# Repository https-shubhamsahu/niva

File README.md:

<p align="center">
  <a href="https://https-shubhamsahu.github.io/niva/"><b>Live dashboard</b></a> ·
  <a href="./startup/niva%20arduino/README.md">Firmware</a> ·
  <a href="./hardware/outputs/NIVA-3D-engineering-prototype/README.md">Rev C.1 hardware</a> ·
  <a href="./startup/niva%20web/src/utils/biomechanicsEngine.ts">Scoring rules</a>
</p>

> Three projects share this insole: the Niva startup, the Aavishkar 2026–27 research entry, and the SIH 2026 problem statement 26213. See [PROJECTS.md](PROJECTS.md) for what belongs to which.

Niva is a smart insole for gait screening. An ESP32 reads four force pads, a piezo disc under the heel and an MPU6050, then streams 20 frames a second to a React dashboard and a Flutter app. Each gait phase, score and alert comes from a threshold in one TypeScript file, so you can point at the exact reading that set off an alert. Niva was shown at Automation Expo in July 2026.

> **Status:** the bench build runs today. The Rev C.1 wearable pod is designed, routed and DRC-clean in KiCad, but it hasn't been built or measured yet. Niva is a research and screening prototype. It isn't a medical device.

## Bench build

The active sketch is [`startup/niva arduino/niva_hardware/niva_hardware.ino`](./startup/niva%20arduino/niva_hardware/niva_hardware.ino).

| Signal | ESP32 pin | Notes |
|---|---|---|
| FSR heel | GPIO 32 | ADC1_CH4 |
| FSR inner (1st metatarsal) | GPIO 33 | ADC1_CH5 |
| FSR outer (5th metatarsal) | GPIO 34 | ADC1_CH6 |
| FSR toe | GPIO 35 | ADC1_CH7 |
| Piezo heel disc | GPIO 36 | ADC1_CH0, the impact channel |
| I2C SDA | GPIO 21 | MPU6050 at `0x68`, SH1106 OLED at `0x3C` |
| I2C SCL | GPIO 22 | shared bus |
| Status LED | GPIO 2 | blinks during tare |

What the firmware does each frame:

- reads every ADC channel 16 times at 12 bits and averages the result
- subtracts a zero-load tare (60 samples, saved in NVS, redone when you send `calibrate` or `tare` over WebSocket or Serial)
- reads pitch, roll and accZ from the MPU6050
- sends one frame every 50 ms to your WebSocket clients and the USB port
- shows Wi-Fi state, tare progress and live channel bars on the OLED

You set up Wi-Fi through a WiFiManager captive portal (`NIVA-GaitGuard-AP`), and the board answers at `ws://niva.local:81` over mDNS.

JSON over WebSocket (`ws://<esp32-ip>:81`):

```json
{"heel":42.00,"inner":68.00,"outer":31.00,"toe":27.00,"piezo":176.00,"pitch":-2.40,"roll":1.30,"accZ":9.72}
```

CSV over USB Serial at 115200 baud:

```text
H,I,O,T,Piezo,Pitch,Roll,AccZ
```

The simpler sketch, `esp32_gaitguard_wifi_manager`, uses hardcoded Wi-Fi credentials and doesn't drive the IMU or the OLED. BLE isn't in any sketch, and the IMU in firmware is the MPU6050 (you won't find BMI270 code here).

## How a step gets scored

The web app runs these rules on every frame in [`biomechanicsEngine.ts`](./startup/niva%20web/src/utils/biomechanicsEngine.ts), and there's no trained model in it. The Flutter app times strides from the firmware's contact edges instead, in [`gait_timing_engine.dart`](./startup/niva%20flutter/lib/core/engine/gait_timing_engine.dart). Here are the web rules, with the default values from the code, so you can check any number on the dashboard by hand:

| Output | Rule |
|---|---|
| Tare check | The first 30 frames must be steady: load range 8 or less, mean load 55 or less, tilt 7 or less, impact 60 or less. After 60 frames it carries on without a baseline. |
| Smoothing | EMA with α = 0.1, a deadband of 2.5 on pressure and 0.8 on angles |
| Contact | stance while the filtered total is above 45 |
| Step | piezo above 200, heel above 80, heel rising by more than 8, and the foot was in swing |
| Cadence | 60 divided by the time between heel strikes (0.2 s to 3 s) |
| Phase | `HEEL_STRIKE` heel > 80 and toe < 40; `MID_STANCE` heel, inner and outer > 50; `TOE_OFF` toe > 80 and heel < 30; `SWING` total < 20 |
| Centre of pressure | load-weighted average of the four pad positions |
| Stability score | 100 - 9 × tilt - 30 × impact level, clamped to 0 to 100 |
| Flags | supination risk when roll > 8 and outer > inner; heel-dominant gait when the heel carries over 70 % of the load for 5 frames; high sway when tilt reaches 6; ischemic pressure risk when the static-load integral passes 50 |

## Rev C.1 wearable pod

The next build swaps the dev board for a pod you wear on the lower shin: ESP32-C3, an MCP3208 ADC, an LSM6DSO32 IMU, a removable battery cartridge, one button and one light. A desk dock charges the cartridges. Every part comes out of a script (FreeCAD 1.1, KiCad 9, Blender 4.5), so you can rebuild the whole design from `hardware/work/`.

<table>
  <tr>
    <td width="50%" valign="top"></td>
    <td width="50%" valign="top"></td>
  </tr>
  <tr>
    <td width="50%" valign="top"></td>
    <td width="50%" valign="top"></td>
  </tr>
</table>

These are CAD renders, not photos. The signal chain inside the pod:

| Board | Size and layers | Routing | KiCad ERC / DRC |
|---|---|---|---|
| Pod | 34 × 48 × 1.0 mm, 4 layers, In1 = GND plane | GND fan-out, Freerouting signals, pours; 547 segments, 126 vias | ERC 0 errors; DRC 0 errors, 0 unconnected |
| Cartridge strip | 3.4 × 30 × 0.8 mm, 2 layers | hand-routed | 0 / 0 |
| Dock | 58 × 56 × 1.6 mm, 2 layers | Freerouting and GND pours | 0 / 0 |
| Insole flex R and L | 0.12 mm polyimide, F.Cu only underfoot | generated paired lanes | 0 / 0 |

What's still open: nothing has been printed, built, powered or measured. RF, sealing, skin contact, cleaning and FSR characterisation are untested, and nobody outside the project has reviewed the design. A clean ERC and DRC is an automated check. It isn't a design review. The pod has a bare-PCB first-article Gerber set for bench bring-up; the rest are review-only. The full list is in [`VERIFICATION-PLAN.md`](./hardware/outputs/NIVA-3D-engineering-prototype/VERIFICATION-PLAN.md) and the [hardware README](./hardware/outputs/NIVA-3D-engineering-prototype/README.md).

## Run it

Don't have the hardware? Open the [live dashboard](https://https-shubhamsahu.github.io/niva/) and switch to **Simulation**. It streams generated gait for six modes (Normal, Parkinson, Stroke, Neuropathy, Foot Drop, Ataxia) through the same engine. The simulated patterns are synthetic, so don't read them as patient data.

Install only what you need for the part you're running:

- **Web:** Node.js 22+ and npm
- **Flutter:** Flutter SDK (Dart 3.3+)
- **Firmware:** Arduino IDE (or another ESP32 Arduino toolchain) with ESP32 board support

### Web dashboard (`niva web`)

```bash
cd "startup/niva web"
npm install
# if peer dependency conflicts appear:
npm install --legacy-peer-deps
npm run dev
```

Other scripts:

```bash
npm run build
npm run preview
npm run lint
```

Optional environment file, `startup/niva web/.env.local`:

```bash
VITE_ESP32_WS_URL=ws://<esp32-ip>:81
VITE_ESP32_WS_RELAY_URL=wss://<your-relay-domain>/ws
VITE_ESP32_WS_RELAY_TARGET_KEY=target
VITE_DATASET_UPLOAD_URL=https://your-api.example.com/upload
VITE_DATASET_UPLOAD_TOKEN=your_optional_bearer_token
```

Optional WebSocket relay, needed when an HTTPS dashboard has to reach a `ws://` ESP32:

```bash
cd "startup/niva web/relay"
npm install
npm start
```

### Flutter app (`niva flutter`)

```bash
cd "startup/niva flutter"
flutter pub get
flutter analyze
flutter test
flutter run
```

The ESP32 endpoint, relay URL and upload URL are runtime settings on the Device tab, not build-time env files.

### Firmware (`niva arduino`)

Open a sketch in Arduino IDE, install the libraries listed in [`startup/niva arduino/README.md`](./startup/niva%20arduino/README.md) (WiFiManager, WebSockets, U8g2), select an ESP32 board and upload:

- **Active hardware sketch:** `startup/niva arduino/niva_hardware/niva_hardware.ino`
- **Simpler hardcoded Wi-Fi sketch:** `startup/niva arduino/esp32_gaitguard_wifi_manager/esp32_gaitguard_wifi_manager.ino`

Open Serial Monitor at **115200** baud, note the printed IP, and point the Flutter Device tab or the web Settings page at `ws://<ESP32_IP>:81`.

## Stack

- **Web:** React 19, TypeScript, Vite, Tailwind, Recharts, IndexedDB, Web Serial
- **Flutter:** Riverpod, Hive, `web_socket_channel`, `fl_chart`
- **Relay:** Node.js and `ws`
- **Deploy:** GitHub Pages through [`.github/workflows/deploy-pages.yml`](./.github/workflows/deploy-pages.yml), which builds `niva web`

There's no application server or database. Your datasets stay in your browser (IndexedDB) or on your phone (Hive). CSV upload to an external research API is optional.

## Repository layout

| Directory | Contents |
|---|---|
| `startup/niva arduino/` | ESP32 firmware: ADC acquisition, tare, IMU, OLED, Wi-Fi and WebSocket |
| `startup/niva web/` | Clinician dashboard, biomechanics views, dataset export and upload, WebSocket relay |
| `startup/niva flutter/` | Patient-facing app: dashboard, device pairing over WebSocket, insights, trends, CSV export |
| `hardware/` | Rev C.1 prototype: FreeCAD pod and dock, KiCad 9 pod, cartridge, dock and insole flex, verification plan, Blender scenes. Not reviewed or released for fabrication. |
| `aavishkar/` | Aavishkar 2026–27 research entry |
| `sih-26213/`, `niva sakshi/` | SIH 2026, problem statement 26213 (Fit India balance tests) |
| `media/` | Shared photos, logos (`media/brand/`), 3D CAD and renders, video scripts |
| `PROJECTS.md` | Which project owns what |
| `SIH2026-DECK-KIT/` | Smart India Hackathon 2026 deck pipeline (HTML slides rendered to PDF) |
| `assets/readme/`, `scripts/` | README diagrams and the script that builds them from the insole template |

## Documentation

| File | Contents |
|---|---|
| [`startup/niva arduino/README.md`](./startup/niva%20arduino/README.md) | Sketches, pin map, libraries |
| [`startup/niva web/README.md`](./startup/niva%20web/README.md) | Dashboard setup, telemetry formats, Pages deploy |
| [`startup/niva web/JUDGES_WALKTHROUGH.md`](./startup/niva%20web/JUDGES_WALKTHROUGH.md) | Algorithm and data walkthrough |
| [`startup/niva flutter/README.md`](./startup/niva%20flutter/README.md) | Flutter setup, architecture, run commands |
| [`startup/niva flutter/DESIGN.md`](./startup/niva%20flutter/DESIGN.md) | Flutter design notes |
| [`startup/niva flutter/BACKEND_LOGIC.md`](./startup/niva%20flutter/BACKEND_LOGIC.md) | Data contract and storage |
| [`hardware/outputs/NIVA-3D-engineering-prototype/README.md`](./hardware/outputs/NIVA-3D-engineering-prototype/README.md) | Rev C.1 boards, CAD, renders, open items |

Niva is an engineering and research screening tool. It is not a medical diagnosis device.

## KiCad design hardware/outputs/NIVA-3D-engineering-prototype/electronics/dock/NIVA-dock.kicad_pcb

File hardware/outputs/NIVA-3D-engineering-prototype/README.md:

# NIVA 3D engineering prototype — Revision C.1

Bilateral gait-sensing research/screening kit with four parts:

- **Insole:** a five-region force insole with a heel PVDF film and a protected flat tail.
- **Pod:** worn on the lower shin (ESP32-C3, MCP3208, LSM6DSO32, removable battery cartridge, one button, one light) and controlled offline from a phone over Bluetooth.
- **Cartridge:** a removable battery cartridge.
- **Dock:** a desk dock that charges bare cartridges.

> **Status: engineering prototype for fit, handling and bench work. Not a released medical device. Not released for fabrication.**
> - Every KiCad board is routed and passes KiCad ERC and DRC. That is an automated check, **not a design review**.
> - Gerbers exist only in `fab-REVIEW-ONLY-NOT-RELEASED/` folders, each with a list of open blockers. The pod's set moved to `fab-PROTOTYPE-PCBWAY/` on 25 Oct: a bare-PCB first article for bench bring-up, with its blockers in `STATUS.txt`.
> - Nothing has been built, powered or measured. Nothing here establishes clinical performance.
> - The sensing concept does **not** measure medial knee contact force.
> - Sealing, skin contact and cleaning are **unverified**: see `VERIFICATION-PLAN.md`.

## What changed in Rev C.1 (this update)

| Open item in Rev C | Rev C.1 resolution | Still open |
|---|---|---|
| Pod PCB unrouted. Freerouting stalled at about 40 open connections, no Gerbers. | GND fan-out first: every GND pad gets its own via to the solid In1 plane. Signals are then autorouted, followed by pours and stitching. **0 DRC errors, 0 unconnected, parity clean.** Review-only Gerbers/drill/placement files. | Independent review, fab DFM, return-path and RF review |
| R33 = 220 Ω made every force reading depend on VEXC, so firmware had to normalise it. | The MCP3208 VREF is now VEXC, so readings are ratiometric in hardware and need **no firmware normalisation**. CH6 becomes a tail-fault monitor. | Bench confirmation |
| Dual clamp diodes not used (contradictory KiCad symbol). | One **BAV199** series pair (SOT-23) on a project symbol that states the data-sheet pinning (1 A1, 2 K2, 3 K1/A2). | Check the reel marking; the PDF host was unreachable, so the pinning comes from two search sources quoting the Nexperia data sheet |
| Battery cell not selected; 300 mAh fit unproven. | EEMB **LP502030** class (230 mAh min, 20.5 × 32 × 5.3 mm max, PCM + NTC). The cartridge is resized around its maximum size plus 8 % swell. **300 mAh does not fit and is not claimed.** | A purchased lot, swelling under cycling, and cell safety evidence |
| Cartridge electronics not designed. | `electronics/cartridge/`: interconnect strip PCB with a series polyfuse and gold dock pads. No active parts. The cell PCM is protection layer 1. | Polyfuse chosen 9 Nov 2026 (Bourns MF-PSMF035X-2, against the cell PCM limits); its series resistance vs radio-burst sag, pad wear |
| Charging dock not designed. | `electronics/dock/`: USB-C, MCP73831 at 100 mA, and a **hardware NTC window** (LM393 → PROG gate). `mechanical/` has a printable dock with a keyed well, tab ledge, snap latch, spring-pin holes and a light pipe. | Spring pins chosen 9 Nov 2026 (Mill-Max 0900-0, well floor lowered to suit); thresholds and termination unmeasured |
| Insole tail could not reach the big toe (A201 tails too short, hold H1). | `electronics/insole/`: an **integrated sensing flex** (R and L). Five printed shunt-mode electrodes and PVDF bond pads, with copper lanes to the heel tab. Only F.Cu and no parts underfoot. A 115 mm tail runs to a stiffened above-collar transition that carries the insert ID resistor. | FSR ink film selection and characterisation, fatigue, lamination |
| No sealing, skin-contact or cleaning claims. | Still **none claimed**. `VERIFICATION-PLAN.md` gives materials, test methods and proposed acceptance criteria. | Every test in that plan |
| Blender PCB close-up read too light green. | Root cause: KiCad 9's GLB writer stores sRGB colours as linear glTF factors. The import now linearises them, and the close-up lights no longer mirror into the glossy mask. | — |

## Contents

```
NIVA-3D-engineering-prototype/
├── README.md                          this file
├── VERIFICATION-PLAN.md               sealing / skin contact / cleaning (and dependent) tests - plan only, no claims
├── mechanical/
│   ├── NIVA-RevC-assembly.FCStd/.step pod assembly: groups Pod_R and Pod_L (left pod at x - 80 mm), incl. routed PCBA
│   ├── NIVA-dock-assembly.FCStd/.step dock assembly with dock PCBA and a seated cartridge
│   ├── STEP-parts/, STL-print-parts/  12 printable parts (01-09 pod, 10-12 dock); STLs in print orientation
│   ├── PRINT-AND-ASSEMBLY.md          materials, orientation, fasteners, clearances, pod/cartridge/dock assembly, open items
│   ├── geometry-validation.json, dock-geometry-validation.json     per-part solid/mesh checks
│   └── interference-report.json, dock-interference-report.json     pairwise interference + functional gaps
├── electronics/
│   ├── NIVA-pod.kicad_pro/.kicad_sch/.kicad_pcb + 2 sub-sheets     pod: 4-layer 34 x 48 mm, ROUTED
│   ├── ELECTRICAL-REVIEW.md           findings, ERC, pin/boot review, analog values, power, PCB, open items
│   ├── exports/                       pod schematic PDF/SVG, ERC, BOM, netlist; pcb/ DRC, assembly PDFs, PCBA STEP+GLB,
│   │                                  fab-REVIEW-ONLY-NOT-RELEASED/ (Gerber, drill, placement, STATUS.txt)
│   ├── cartridge/  NIVA-cartridge.*   interconnect strip (hand-routed) + exports/ (same structure)
│   ├── dock/       NIVA-dock.*        charging dock (autorouted) + exports/
│   ├── insole/     NIVA-insole-R.*, NIVA-insole-L.*   sensing flex, right/left medium + exports/
│   ├── 3dmodels/                      STEP models (KiCad library, Espressif, *_ENVELOPE stand-ins)
│   └── work-routing/                  Specctra DSN/SES + Freerouting logs (the sessions actually imported)
├── renders/                           11 captioned images: 01-07 Blender scenes, pcb_* KiCad raytraces; raw/, pcb-raw/ originals
└── blender/
    ├── NIVA-RevC-scenes.blend         editable Blender 4.5 file: 7 scenes + hidden library collections
    └── 01..07_*.glb                   glTF binary of each scene
```

## Opening the files

- **FreeCAD 1.1:** open `mechanical/NIVA-RevC-assembly.FCStd` or `NIVA-dock-assembly.FCStd`. Objects carry `Material`, `Kind` and `Note` properties. The models are solid assemblies generated by script, so change dimensions in `work/niva_layout.py` and re-run the generators.
- **KiCad 9:** open any `.kicad_pro`.
  - Project libraries resolve through `${KIPRJMOD}`; 3D models through `${KIPRJMOD}/3dmodels` (pod) or `${KIPRJMOD}/../3dmodels`.
  - The insole flex boards use negative y coordinates: the insole frame has the heel at y = 100 mm and the toe above it.
- **Blender 4.5:** open `blender/NIVA-RevC-scenes.blend`, which has scenes `01_Pod_Assembled` … `07_Insole_Flex`. The `LIB_*` collections hold the source meshes and GLBs (render-hidden).
- **Any glTF viewer:** `blender/*.glb` and `electronics/**/exports/pcb/*-PCBA.glb`.

## Boards at a glance

| Board | Size / layers | Routing | KiCad ERC / DRC (schematic parity on) |
|---|---|---|---|
| Pod | 34 × 48 × 1.0 mm, 4 layers (In1 = GND plane) | GND fan-out, then Freerouting signals, then pours; 547 segments, 126 vias (0.5 / 0.2 mm since 25 Oct) | 0 errors, 1 reviewed warning / **0 errors, 0 unconnected**, 3 silk warnings (module outline at the antenna edge); rechecked in KiCad 10.0.7 on 25 Oct |
| Cartridge strip | 3.4 × 30 × 0.8 mm, 2 layers | hand-routed | 0 / 0, 0 unconnected |
| Dock | 58 × 56 × 1.6 mm, 2 layers | Freerouting + GND pours | 0 / 0, 0 unconnected |
| Insole flex R, L | 0.12 mm polyimide; F.Cu only underfoot | generated paired lanes; B.Cu only at the above-collar transition | 0 / 0, 0 unconnected |

## Printing and assembly

See `mechanical/PRINT-AND-ASSEMBLY.md`. It covers:
- material and print orientation for all 12 printed parts;
- fasteners for the pod and dock;
- nominal clearances measured in CAD;
- pod, cartridge and dock assembly sequences;
- the list of unverified fits and safety mechanisms.

## Complete vs provisional

| Area | Complete in this package | Provisional / open |
|---|---|---|
| Pod enclosure | Rev C solids and printable STL/STEP for R and L; interference audit against the routed PCBA (only the intended spring preload overlaps) | Every 0.2 mm fit, sealing, latch and screw durability, skin contact, cleaning |
| Battery | Selected cell class; cartridge cup, lid, strip PCB, pads and windows; charge-only-when-removed concept | Purchased lot, swelling, lid welding, cell safety evidence |
| Dock | Schematic, routed PCB and printable enclosure; audit shows only the intended spring-pin compression | Spring-pin part, measured thresholds and termination, latch life |
| Schematic | Connected hierarchy, ratiometric ADC, reviewed values, ERC-clean | Bench validation of the analog front end, datasheet re-checks listed in the review |
| Pod PCB | Routed, DRC-clean, review-only fab data | Independent review, fab DFM, RF and return-path review |
| Insole | Sensing flex R/L (schematic, routed layout, review-only fab data); visual insert from the 1:1 fit template | FSR film, lamination, fatigue, sweat ingress, other sizes (no automatic grading) |
| Renders | 7 Blender scenes + 4 KiCad raytraces, captioned with status | Soft goods (strap, tail) are parametric bands, not CAD parts |

## Regenerating

Everything is script-generated. From `hardware/work/` (paths below are the Linux build used for this package: KiCad 9.0.9 in Docker via a `kicad9` wrapper, FreeCAD 1.1.3, `bpy` 4.5, Freerouting 2.1.0 via `niva-route`, which is Freerouting headless on `work-routing/<name>.dsn`):

```sh
python3 build_niva_schematic_revC.py            # pod schematic + project rules
python3 build_niva_power_schematics.py          # cartridge + dock schematics
python3 build_niva_insole_flex.py               # insole flex schematics, footprints, lane geometry (needs shapely)
# netlists: kicad-cli sch export netlist --format kicadsexpr -o <dir>/exports/<name>.net <name>.kicad_sch
kicad9 python3 build_niva_pcb.py place <pod|cartridge|dock|insole-R|insole-L>
niva-route NIVA-pod 100 900                     # (and NIVA-dock); cartridge and insoles are hand/generated
kicad9 python3 build_niva_pcb.py finalize pod "<status>" ../outputs/.../work-routing/NIVA-pod.ses
kicad9 python3 build_niva_pcb.py finalize cartridge "<status>" hand     # likewise insole-R / insole-L
python3 export_niva_electronics.py              # ERC, DRC, PDFs, BOMs, STEP/GLB, review-only fab data
./render_kicad_pcb.sh                           # KiCad raytraces of the pod
PYTHONPATH=/opt/freecad/lib /opt/freecad/bin/python build_niva_envelopes.py   # spring-pin envelope model
PYTHONPATH=/opt/freecad/lib /opt/freecad/bin/python build_niva_cad_revC.py    # pod enclosure + audit
PYTHONPATH=/opt/freecad/lib /opt/freecad/bin/python build_niva_dock_cad.py    # dock enclosure + audit
/opt/bpyenv/bin/python build_niva_scenes.py && python3 caption_renders.py
```

- **UUIDs:** the schematic generators use deterministic UUIDs, so re-running them keeps each schematic and PCB linked.
- **Autorouting:** Freerouting is not deterministic. The committed `.ses` files are the ones that were imported and DRC-checked; a new routing run must be re-checked.
- **Pod via drills:** on 25 Oct 2026 the pod's 126 vias were edited in the board file from 0.25 to 0.2 mm drill (pad still 0.5 mm) for PCBWay's 0.15 mm annular-ring rule. `build_niva_pcb.py` still writes 0.25 mm, so re-apply the change after any regeneration. The cartridge and dock boards still use 0.25 mm drills.

## Sources and third-party assets

- **Engineering brief:** "Niva prototype blueprint: from bench insole to health-camp kit", draft v0.1 (`hardware/brief/engineering-brief.txt`). Its component choices were reviewed, not assumed validated. Its prices, literature figures and unpublished study results are not adopted here.
- **Rev A vector blueprints:** `outputs/niva-vector-blueprints/`. The 1:1 fit template supplies the insole outline, the sensor-region centres and the heel tab used by the flex and the renders.
- **Espressif KiCad libraries** (ESP32-C3-MINI-1 symbol, footprint and STEP model): github.com/espressif/kicad-libraries, commit `dd76561`. CC-BY-SA 4.0 with the design-use exception. The symbol was converted to KiCad 9 format; the footprint and model are unmodified.
- **KiCad 9 libraries:** symbols and footprints from KiCad 9.0.9. 3D models from gitlab.com/kicad/libraries/kicad-packages3D, tag 9.0.0 (KMR2 from `master`). CC-BY-SA 4.0 with the design-use exception.
- **Simplified envelopes (not supplier models; orange in the renders):**
  - `TDFN-8-2x2mm_ENVELOPE.step` (MAX17048);
  - `NIVA_SpringContact_1x04_ENVELOPE.step` (pod J2);
  - `NIVA_SpringPin_1x03_ENVELOPE.step` (dock J2);
  - the cell, drawn at its published maximum size.
- **Component data used in Rev C.1** (from web search, because manufacturer sites were blocked from the build environment):
  - MCP3208 VREF range 0.25 V–VDD and VREF current (Microchip DS21298);
  - MCP73831 PROG behaviour and I_REG = 1000 V / R_PROG (Microchip);
  - LM393 input common-mode behaviour (TI);
  - EEMB LP502030 size and capacity (EEMB listing);
  - BAV199 pinning and leakage (Nexperia data sheet, as quoted in search results).

  Confirm each against the current PDF before any release.
- **Tools:**
  - FreeCAD 1.1.3.
  - KiCad 9.0.9 (Docker `kicad/kicad:9.0`).
  - Blender 4.5.14 LTS (`bpy`).
  - Freerouting 2.1.0.
  - shapely 2.1 (flex geometry).
  - DejaVu Sans font (CAD lettering).

## Checks actually completed

- **KiCad CLI, every board:**
  - ERC with all severities;
  - DRC with schematic parity;
  - netlist, BOM, PDF, STEP and GLB exports;
  - review-only Gerber, drill and placement exports;
  - raytraced renders of the pod.
- **FreeCAD:**
  - Every printable part is one valid solid with a closed, manifold mesh.
  - Pairwise interference audits cover the right pod, including the routed PCBA and the cartridge internals, and the dock with a seated cartridge.
  - The only intersections are the intended spring-contact and spring-pin compressions.
- **Insole flex:** the lane corridors stay at least 1 mm inside the 1:1 insole outline, except where the lanes intentionally cross the edge into the heel tab. This is checked by the generator.
- **Blender:** all scenes were rendered and visually inspected. The KiCad GLB colour error was diagnosed and fixed at the import.
- **Not done:**
  - any physical print or electrical build;
  - any measurement;
  - RF test;
  - sealing, skin, pressure or cleaning tests;
  - FSR characterisation;
  - independent design review.

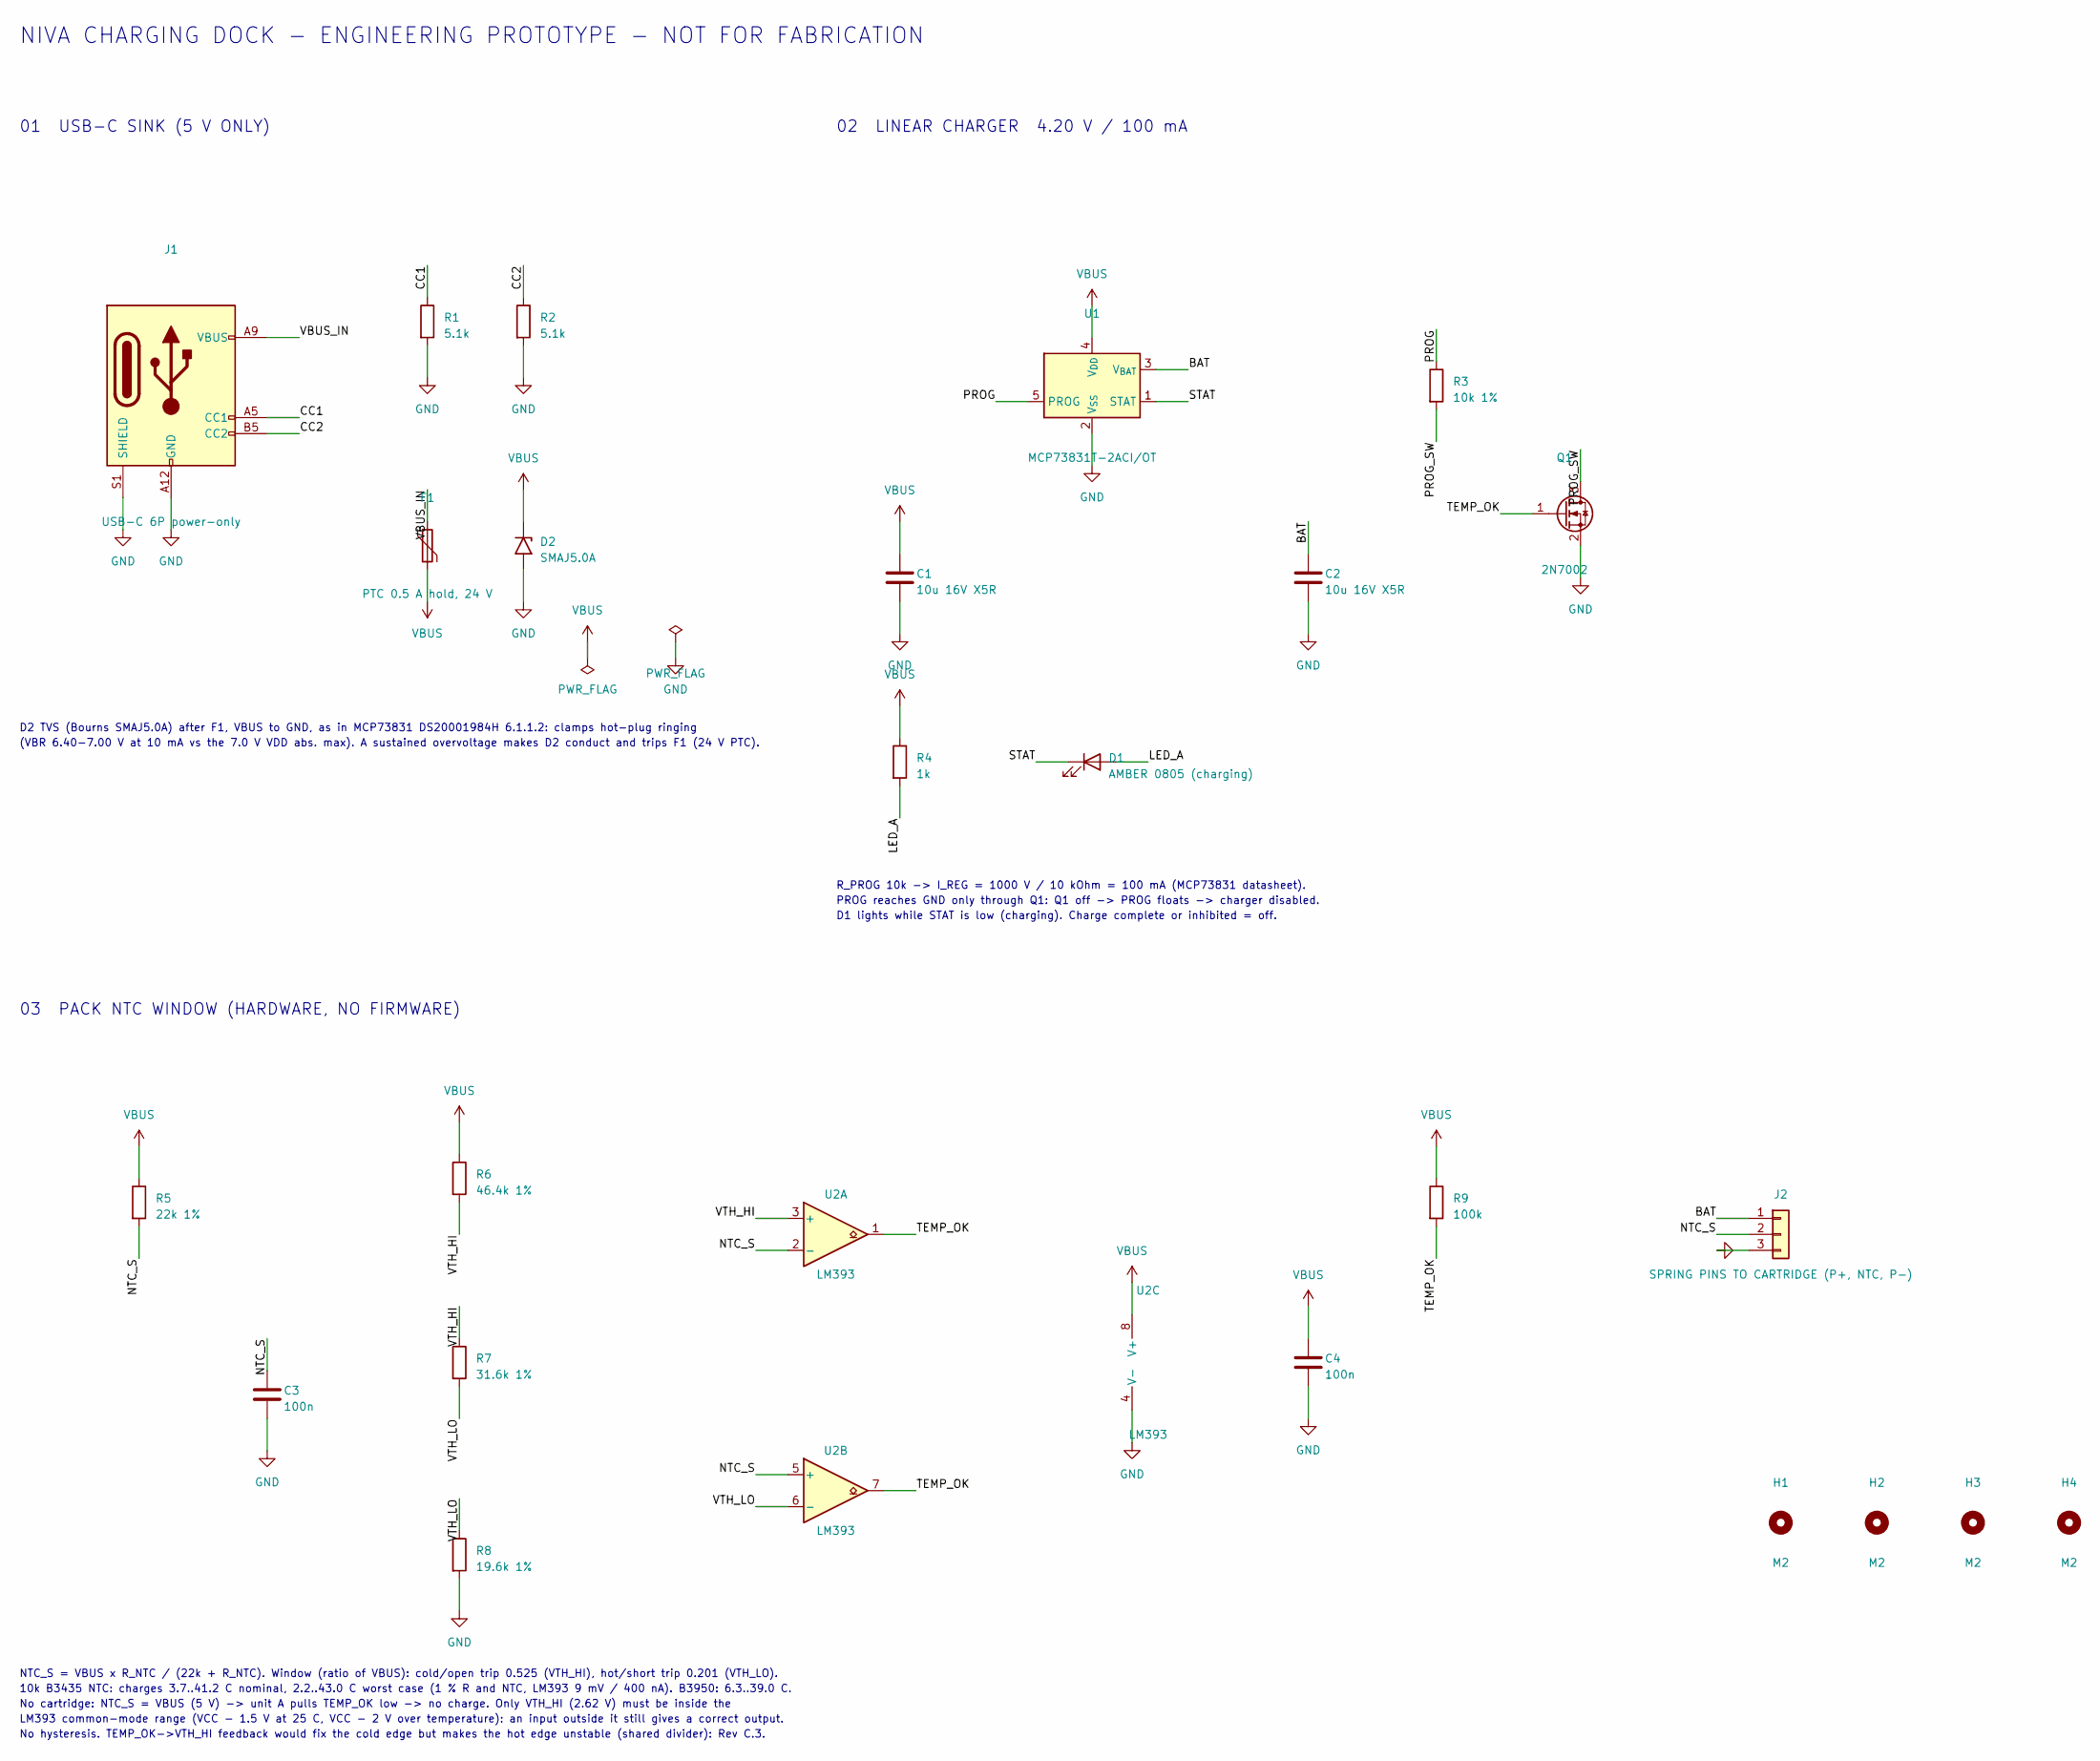
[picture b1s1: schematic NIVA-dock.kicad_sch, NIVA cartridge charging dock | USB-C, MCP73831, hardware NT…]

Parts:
C1, C2: 10u 16V X5R; C_0805_2012Metric; MPN Murata GRM21BR61C106KE15L
C3, C4: 100n; C_0603_1608Metric
D1: AMBER 0805 (charging); LED_0805_2012Metric
D2: SMAJ5.0A; D_SMA; MPN Bourns SMAJ5.0A
F1: PTC 0.5 A hold, 24 V; Fuse_1206_3216Metric; MPN Bourns MF-NSMF050/24X-2
H1, H2, H3, H4: M2; MountingHole_2.2mm_M2
J1: USB-C 6P power-only; USB_C_Receptacle_GCT_USB4125-xx-x_6P_TopMnt_Horizontal; MPN GCT USB4125-GF-A-0190
J2: SPRING PINS TO CARTRIDGE (P+, NTC, P-); SpringPins_1x03_P6.0mm_Vertical; MPN Mill-Max 0900-0-15-20-76-14-11-0 (3 pcs)
Q1: 2N7002; SOT-23
R1, R2: 5.1k; R_0603_1608Metric
R3: 10k 1%; R_0603_1608Metric
R4: 1k; R_0603_1608Metric
R5: 22k 1%; R_0603_1608Metric
R6: 46.4k 1%; R_0603_1608Metric; MPN Yageo RC0603FR-0746K4L
R7: 31.6k 1%; R_0603_1608Metric; MPN Yageo RC0603FR-0731K6L
R8: 19.6k 1%; R_0603_1608Metric; MPN Yageo RC0603FR-0719K6L
R9: 100k; R_0603_1608Metric
U1: MCP73831T-2ACI/OT; SOT-23-5; MPN MCP73831T-2ACI/OT
U2: LM393; SOIC-8_3.9x4.9mm_P1.27mm

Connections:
/BAT: C2.1, J2.1, U1.3 (V_{BAT})
/CC1: J1.A5 (CC1), R1.1
/CC2: J1.B5 (CC2), R2.1
/LED_A: D1.2 (A), R4.2
/NTC_S: C3.1, J2.2, R5.2, U2.2 (-), U2.5 (+)
/PROG: R3.1, U1.5 (PROG)
/PROG_SW: Q1.3 (D), R3.2
/STAT: D1.1 (K), U1.1 (STAT)
/TEMP_OK: Q1.1 (G), R9.2, U2.1, U2.7
/VBUS_IN: F1.1, J1.A9 (VBUS), J1.B9 (VBUS)
/VTH_HI: R6.2, R7.1, U2.3 (+)
/VTH_LO: R7.2, R8.1, U2.6 (-)
GND: C1.2, C2.2, C3.2, C4.2, D2.2 (A2), J1.A12 (GND), J1.B12 (GND), J1.S1 (SHIELD), J2.3, Q1.2 (S), R1.2, R2.2, R8.2, U1.2 (V_{SS}), U2.4 (V-)
VBUS: C1.1, C4.1, D2.1 (A1), F1.2, R4.1, R5.1, R6.1, R9.1, U1.4 (V_{DD}), U2.8 (V+)

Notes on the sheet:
NIVA CHARGING DOCK - ENGINEERING PROTOTYPE - NOT FOR FABRICATION
01 USB-C SINK (5 V ONLY)
02 LINEAR CHARGER 4.20 V / 100 mA
R_PROG 10k -> I_REG = 1000 V / 10 kOhm = 100 mA (MCP73831 datasheet).
PROG reaches GND only through Q1: Q1 off -> PROG floats -> charger disabled.
D1 lights while STAT is low (charging). Charge complete or inhibited = off.
03 PACK NTC WINDOW (HARDWARE, NO FIRMWARE)
NTC_S = VBUS x R_NTC / (22k + R_NTC). Window (ratio of VBUS): cold/open trip 0.525 (VTH_HI), hot/short trip 0.201 (VTH_LO).
10k B3435 NTC: charges 3.7..41.2 C nominal, 2.2..43.0 C worst case (1 % R and NTC, LM393 9 mV / 400 nA). B3950: 6.3..39.0 C.
No cartridge: NTC_S = VBUS (5 V) -> unit A pulls TEMP_OK low -> no charge. Only VTH_HI (2.62 V) must be inside the
LM393 common-mode range (VCC - 1.5 V at 25 C, VCC - 2 V over temperature): an input outside it still gives a correct output.
No hysteresis. TEMP_OK->VTH_HI feedback would fix the cold edge but makes the hot edge unstable (shared divider): Rev C.3.
D2 TVS (Bourns SMAJ5.0A) after F1, VBUS to GND, as in MCP73831 DS20001984H 6.1.1.2: clamps hot-plug ringing
(VBR 6.40-7.00 V at 10 mA vs the 7.0 V VDD abs. max). A sustained overvoltage makes D2 conduct and trips F1 (24 V PTC).

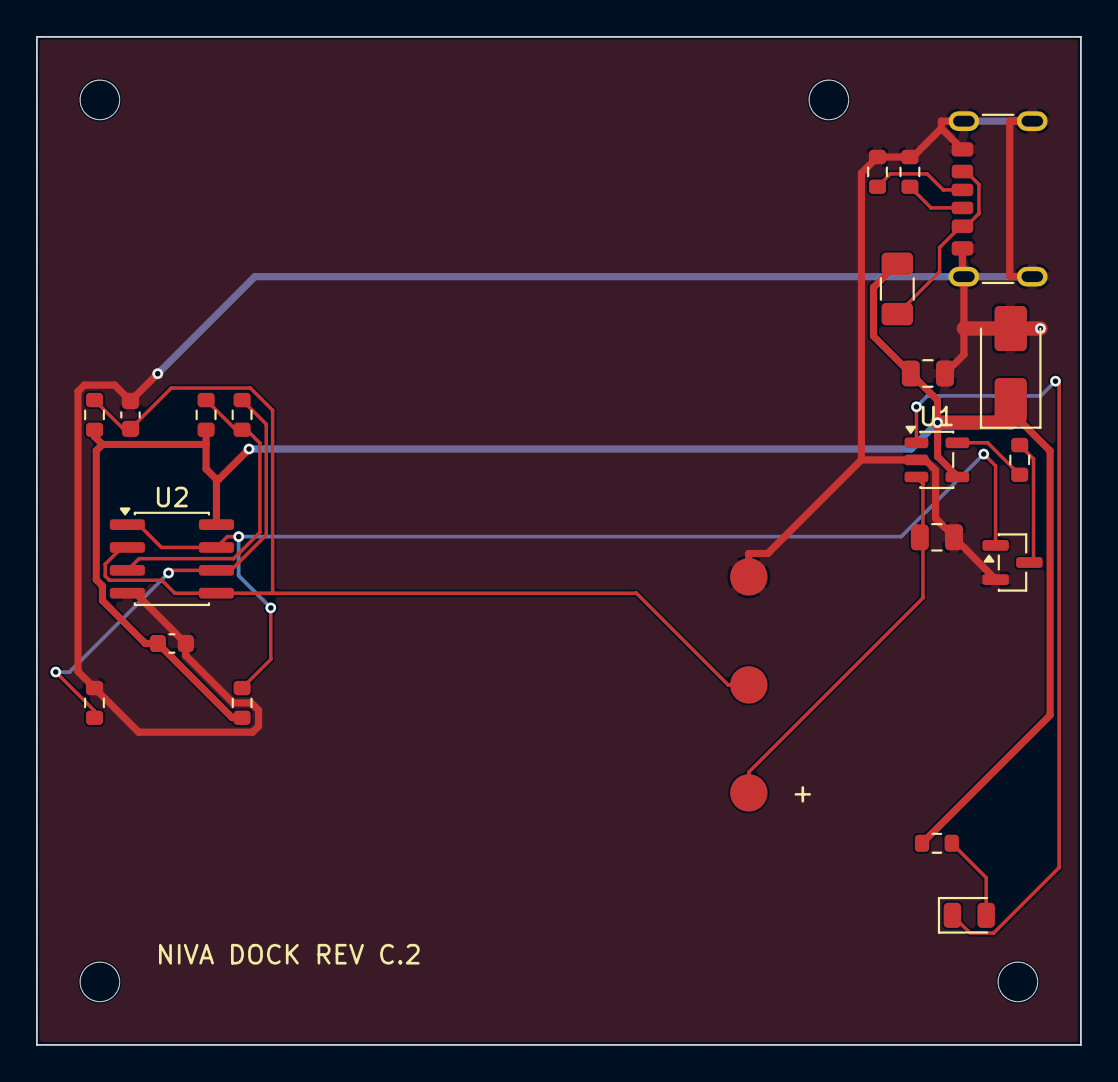
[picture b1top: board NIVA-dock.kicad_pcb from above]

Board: 2 copper layers, 58.0 x 56.0 mm, 25 parts (0 on the bottom side), 14 nets.

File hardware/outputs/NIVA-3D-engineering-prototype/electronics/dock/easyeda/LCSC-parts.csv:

Ref,Value,KiCad footprint,Design MPN,LCSC (use),LCSC MPN as listed,JLC class,Note
"C1,C2",10u 16V X5R,C_0805_2012Metric,Murata GRM21BR61C106KE15L,C77075,muRata GRM21BR61C106KE15L,Extended,"Basic alt C15850 Samsung CL21A106KAYNNNE 10u 25V X5R, same land"
"C3,C4",100n,C_0603_1608Metric,,C1591,Samsung CL10B104KB8NNNC (50V X7R),Basic,"Was C14663 YAGEO CC0603KRX7R9BB104, 0 LCSC stock on 11 Nov 2026"
D1,AMBER 0805 (charging),LED_0805_2012Metric,,C84262,NationStar NCD0805O1 (orange 589-610 nm),Extended,No amber 0805 found; Basic yellow alt C2296 KENTO KT-0805Y
D2,SMAJ5.0A,D_SMA,Bourns SMAJ5.0A,C151932,BORN SMAJ5.0A,Extended,"Listed maker is BORN, not Bourns; MDD alt C113952; Bourns SMAJ5.0A-Q C1869355 showed 0 stock"
F1,PTC 0.5 A hold 24 V,Fuse_1206_3216Metric,Bourns MF-NSMF050/24X-2,C27856618,BOURNS MF-NSMF050/24X-2,Extended,Not C75464 (MF-NSMF050-2 is 13.2 V)
J1,USB-C 6P power-only,USB_C_Receptacle_GCT_USB4125-xx-x_6P_TopMnt_Horizontal,GCT USB4125-GF-A-0190,C5246813,GCT USB4125-GF-A-0190,Extended,Exact MPN
J2,Spring pins x3 (P+ NTC P-),NIVA_power:SpringPins_1x03_P6.0mm_Vertical,Mill-Max 0900-0-15-20-76-14-11-0 (3 pcs),C21211881,Mill-Max 0900-0-15-20-76-14-11-0,Extended,0 LCSC stock on 11 Nov 2026. Keep this part and footprint: buy 15 from DigiKey or Mouser and hand-solder after assembly (JLC difficulty High anyway)
Q1,2N7002,SOT-23,,C8545,JSCJ 2N7002,Basic,
"R1,R2",5.1k,R_0603_1608Metric,,C23186,UNI-ROYAL 0603WAF5101T5E,Basic,
R3,10k 1%,R_0603_1608Metric,,C25804,UNI-ROYAL 0603WAF1002T5E,Basic,
R4,1k,R_0603_1608Metric,,C21190,UNI-ROYAL 0603WAF1001T5E,Basic,
R5,22k 1%,R_0603_1608Metric,,C31850,UNI-ROYAL 0603WAF2202T5E,Basic,
R6,46.4k 1%,R_0603_1608Metric,Yageo RC0603FR-0746K4L,C165747,YAGEO RC0603FR-0746K4L,Extended,Exact MPN
R7,31.6k 1%,R_0603_1608Metric,Yageo RC0603FR-0731K6L,C25967,UNI-ROYAL 0603WAF3162T5E,not checked,"Substitute: Yageo RC0603FR-0731K6L C185339 had 0 LCSC stock on 11 Nov 2026; same value, 1%, 0603"
R8,19.6k 1%,R_0603_1608Metric,Yageo RC0603FR-0719K6L,C22898,UNI-ROYAL 0603WAF1962T5E,Extended (EasyEDA library),"Substitute: Yageo -0719K6L not on LCSC; Stackpole C2484079 has no EasyEDA library device, so C22898 (same value, 1%, 0603; 4,600 in stock on 11 Nov 2026)"
R9,100k,R_0603_1608Metric,,C25803,UNI-ROYAL 0603WAF1003T5E,Basic,
U1,MCP73831T-2ACI/OT,SOT-23-5,MCP73831T-2ACI/OT,C424093,MICROCHIP MCP73831T-2ACI/OT,Extended,Not C38066 (MCP73832)
U2,LM393,SOIC-8_3.9x4.9mm_P1.27mm,,C7955,onsemi LM393DR2G,Basic,TI LM393DR is C67470 (Extended)

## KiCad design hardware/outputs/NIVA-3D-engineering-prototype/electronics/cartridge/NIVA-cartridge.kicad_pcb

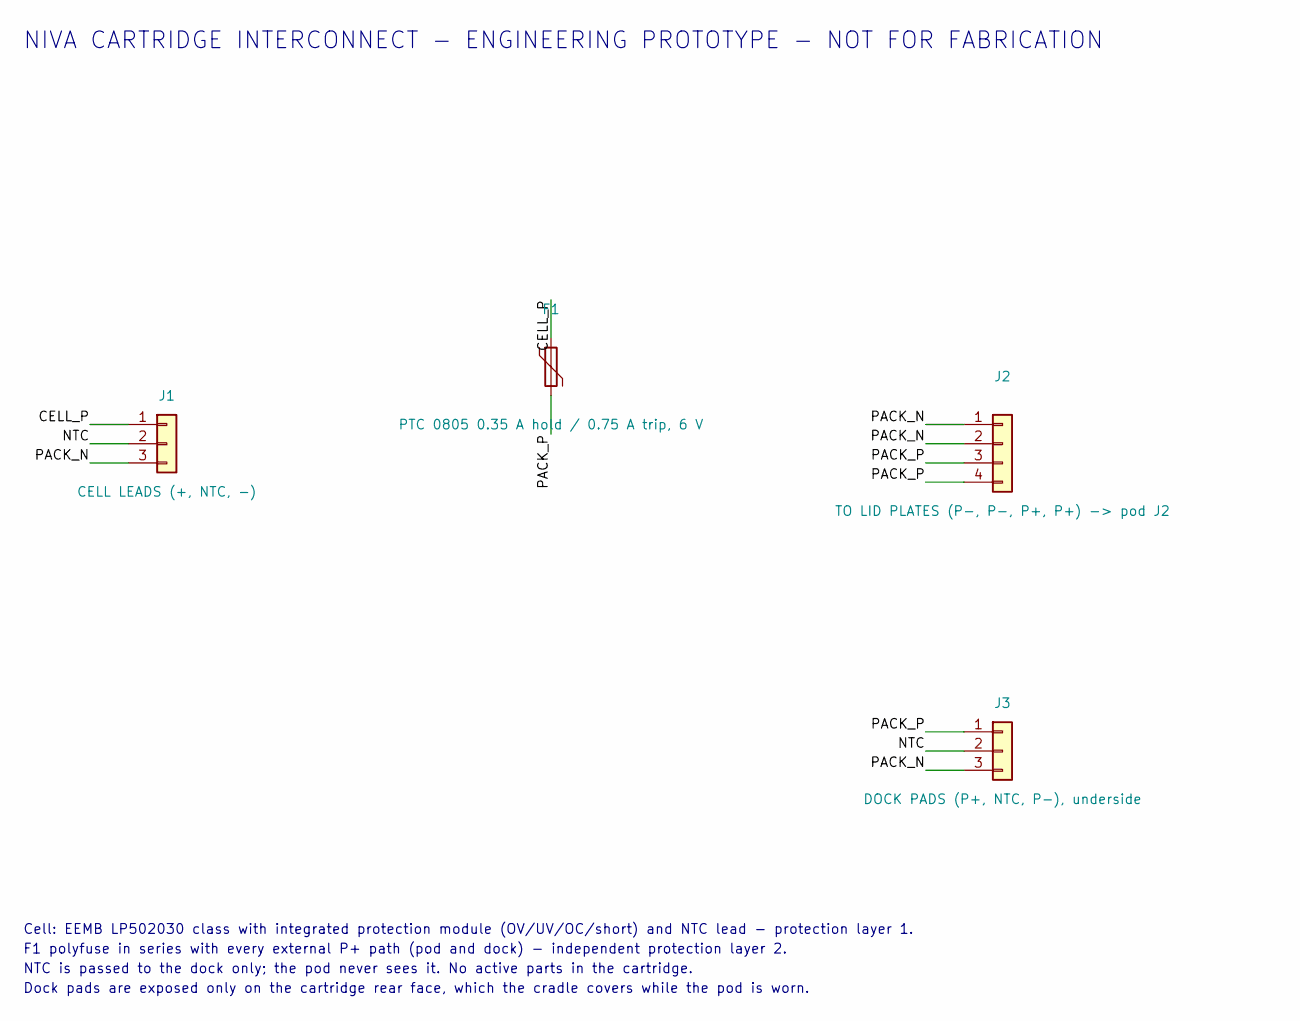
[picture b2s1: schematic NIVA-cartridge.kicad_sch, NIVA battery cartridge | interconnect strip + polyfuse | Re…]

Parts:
F1: PTC 0805 0.35 A hold / 0.75 A trip, 6 V; Fuse_0805_2012Metric; MPN Bourns MF-PSMF035X-2
J1: CELL LEADS (+, NTC, -); WirePads_1x03_P1.8mm
J2: TO LID PLATES (P-, P-, P+, P+) -> pod J2; WirePads_1x04_P1.7mm
J3: DOCK PADS (P+, NTC, P-), underside; ContactPads_1x03_P6.0mm

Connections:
/CELL_P: F1.1, J1.1
/NTC: J1.2, J3.2
/PACK_N: J1.3, J2.1, J2.2, J3.3
/PACK_P: F1.2, J2.3, J2.4, J3.1

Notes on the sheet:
NIVA CARTRIDGE INTERCONNECT - ENGINEERING PROTOTYPE - NOT FOR FABRICATION
Cell: EEMB LP502030 class with integrated protection module (OV/UV/OC/short) and NTC lead - protection layer 1.
F1 polyfuse in series with every external P+ path (pod and dock) - independent protection layer 2.
NTC is passed to the dock only; the pod never sees it. No active parts in the cartridge.
Dock pads are exposed only on the cartridge rear face, which the cradle covers while the pod is worn.

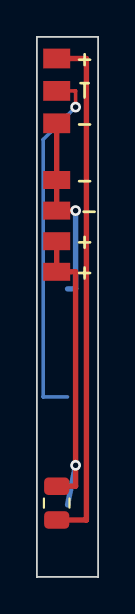
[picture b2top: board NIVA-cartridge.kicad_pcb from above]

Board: 2 copper layers, 3.4 x 30.0 mm, 4 parts (1 on the bottom side), 4 nets.

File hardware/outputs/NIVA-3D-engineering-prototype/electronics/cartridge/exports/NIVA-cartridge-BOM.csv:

"Reference","Value","Footprint","MPN","QUANTITY"
"F1","PTC 0805 0.35 A hold / 0.75 A trip, 6 V","Fuse:Fuse_0805_2012Metric","Bourns MF-PSMF035X-2","1"
"J1","CELL LEADS (+, NTC, -)","NIVA_power:WirePads_1x03_P1.8mm","","1"
"J2","TO LID PLATES (P-, P-, P+, P+) -> pod J2","NIVA_power:WirePads_1x04_P1.7mm","","1"
"J3","DOCK PADS (P+, NTC, P-), underside","NIVA_power:ContactPads_1x03_P6.0mm","","1"

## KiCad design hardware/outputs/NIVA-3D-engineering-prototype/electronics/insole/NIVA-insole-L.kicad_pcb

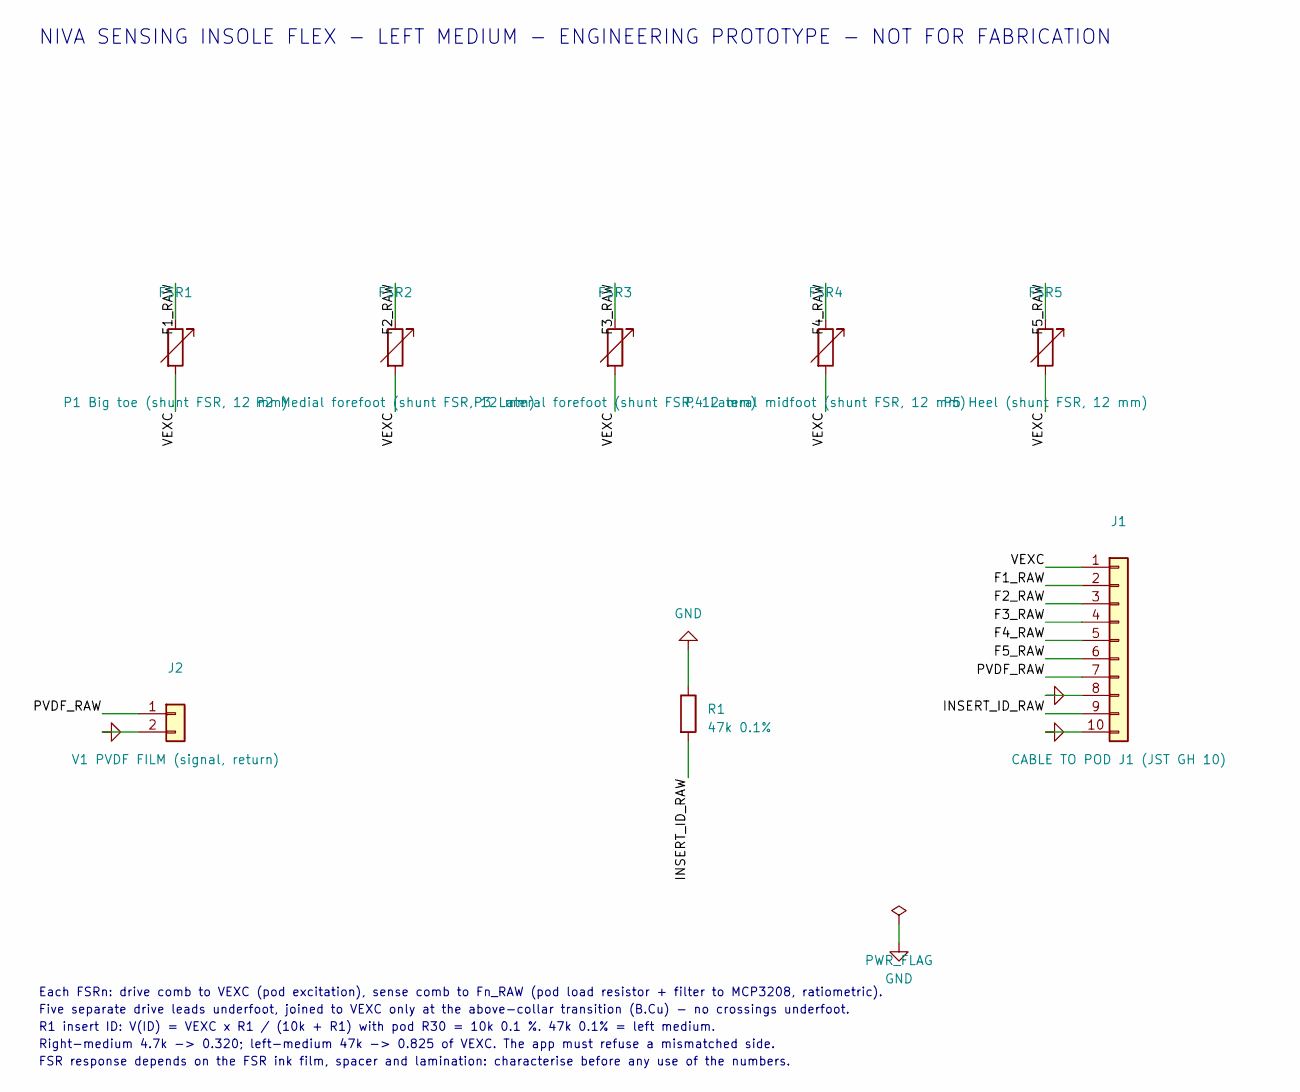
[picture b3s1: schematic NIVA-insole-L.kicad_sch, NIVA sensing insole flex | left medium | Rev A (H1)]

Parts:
FSR1: P1 Big toe (shunt FSR, 12 mm); FSR_Interdigitated_D12mm
FSR2: P2 Medial forefoot (shunt FSR, 12 mm); FSR_Interdigitated_D12mm
FSR3: P3 Lateral forefoot (shunt FSR, 12 mm); FSR_Interdigitated_D12mm
FSR4: P4 Lateral midfoot (shunt FSR, 12 mm); FSR_Interdigitated_D12mm
FSR5: P5 Heel (shunt FSR, 12 mm); FSR_Interdigitated_D12mm
J1: CABLE TO POD J1 (JST GH 10); WirePads_1x10_P2.0mm_LaneOrder
J2: V1 PVDF FILM (signal, return); PVDF_BondPads_2x6x2mm
R1: 47k 0.1%; R_0603_1608Metric; MPN 0603 thin film 47k 0.1% (left medium co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

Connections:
/F1_RAW: FSR1.1, J1.2
/F2_RAW: FSR2.1, J1.3
/F3_RAW: FSR3.1, J1.4
/F4_RAW: FSR4.1, J1.5
/F5_RAW: FSR5.1, J1.6
/INSERT_ID_RAW: J1.9, R1.2
/PVDF_RAW: J1.7, J2.1
/VEXC: FSR1.2, FSR2.2, FSR3.2, FSR4.2, FSR5.2, J1.1
GND: J1.8, J1.10, J2.2, R1.1

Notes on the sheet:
NIVA SENSING INSOLE FLEX - LEFT MEDIUM - ENGINEERING PROTOTYPE - NOT FOR FABRICATION
Each FSRn: drive comb to VEXC (pod excitation), sense comb to Fn_RAW (pod load resistor + filter to MCP3208, ratiometric).
Five separate drive leads underfoot, joined to VEXC only at the above-collar transition (B.Cu) - no crossings underfoot.
R1 insert ID: V(ID) = VEXC x R1 / (10k + R1) with pod R30 = 10k 0.1 %. 47k 0.1% = left medium.
Right-medium 4.7k -> 0.320; left-medium 47k -> 0.825 of VEXC. The app must refuse a mismatched side.
FSR response depends on the FSR ink film, spacer and lamination: characterise before any use of the numbers.

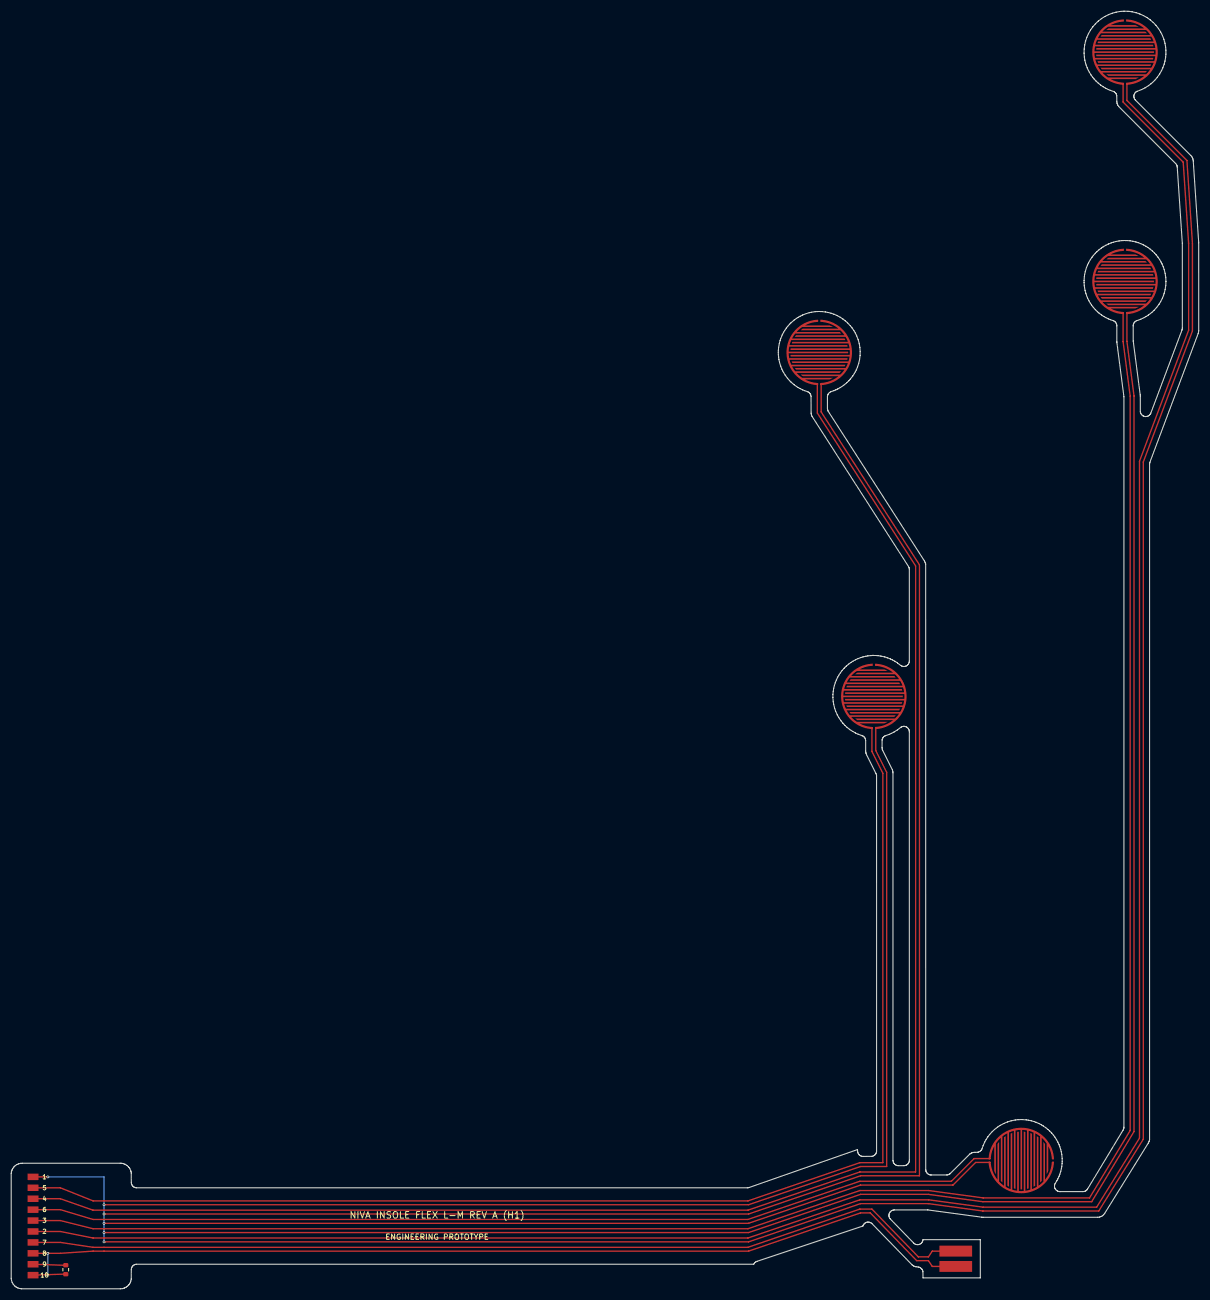
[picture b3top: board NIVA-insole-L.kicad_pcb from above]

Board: 2 copper layers, 217.5 x 234.0 mm, 8 parts (0 on the bottom side), 9 nets.

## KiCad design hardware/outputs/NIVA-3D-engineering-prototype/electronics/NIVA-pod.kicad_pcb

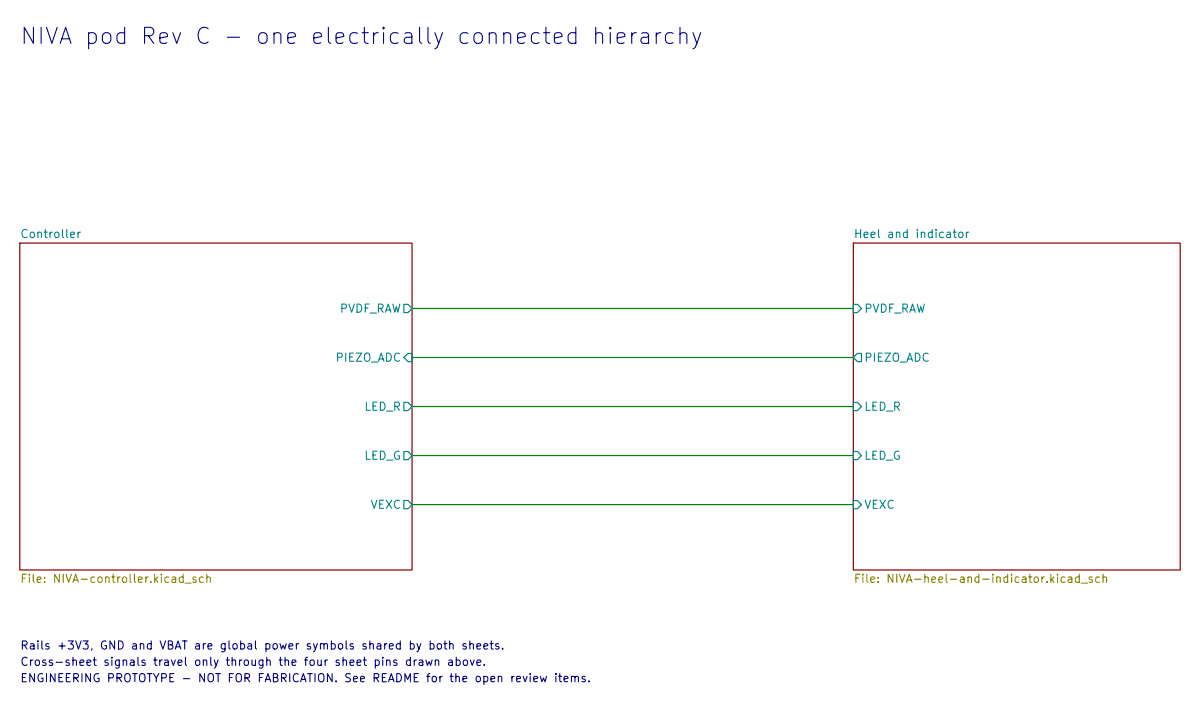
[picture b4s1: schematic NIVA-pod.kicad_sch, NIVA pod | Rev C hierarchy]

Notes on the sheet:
NIVA pod Rev C - one electrically connected hierarchy
Rails +3V3, GND and VBAT are global power symbols shared by both sheets.
Cross-sheet signals travel only through the four sheet pins drawn above.
ENGINEERING PROTOTYPE - NOT FOR FABRICATION. See README for the open review items.
